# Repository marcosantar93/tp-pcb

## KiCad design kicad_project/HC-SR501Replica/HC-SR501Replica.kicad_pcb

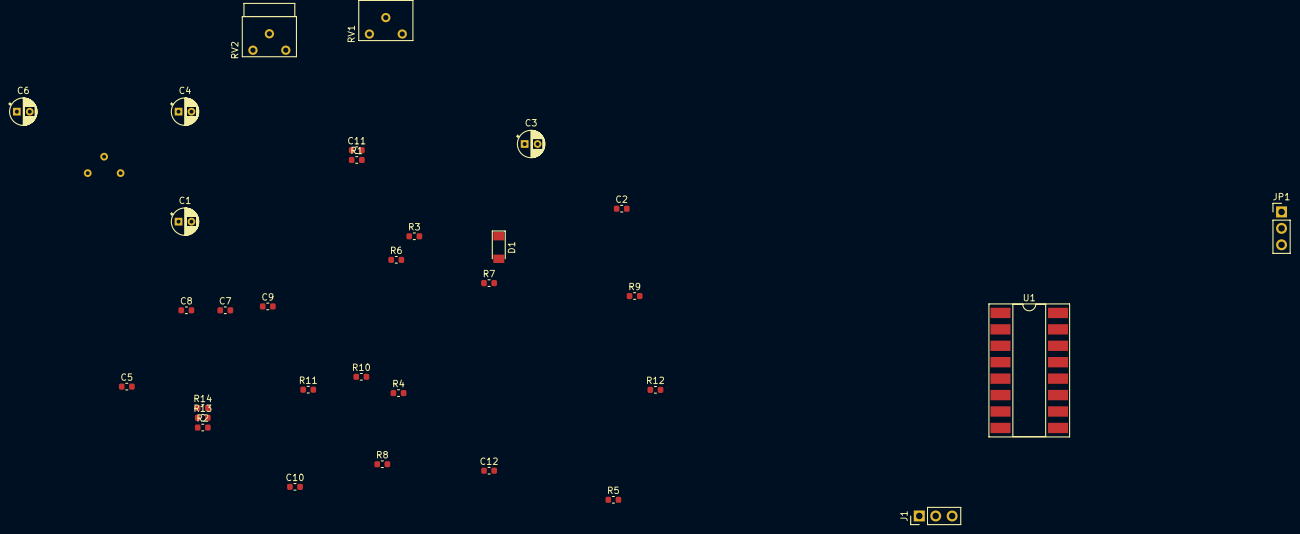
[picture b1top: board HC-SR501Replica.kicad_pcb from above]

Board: 2 copper layers, 33 parts (1 on the bottom side), 26 nets, no tracks yet.

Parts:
C1: 22μ; CP_Radial_D4.0mm_P2.00mm
C2, C5, C8, C10, C11: 103p; C_0603_1608Metric
C3, C4, C6: 47μ; CP_Radial_D4.0mm_P2.00mm
C7, C12: 104p; C_0603_1608Metric
C9: 502p; C_0603_1608Metric
D1: D; D_MiniMELF
J1: Conn_01x03; PinHeader_1x03_P2.54mm_Vertical
JP1: Jumper_3_Bridged12; PinHeader_1x03_P2.54mm_Vertical
PIR1: ZSBG446671; PIR
R1, R13: 10K; R_0603_1608Metric
R2, R4, R6: 18K; R_0603_1608Metric
R3: 47K; R_0603_1608Metric
R5, R10, R12, R14: 1M; R_0603_1608Metric
R7: 12K; R_0603_1608Metric
R8: 470K; R_0603_1608Metric
R9: 6.8K; R_0603_1608Metric
R11: R_PHOTO; R_0603_1608Metric
RV1, RV2: 1M; Potentiometer_Bourns_3339W_Horizontal
U1: BISS0001; DIP-16_W8.89mm_SMDSocket_LongPads

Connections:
+3V3: C1.1, JP1.3, R1.2, U1.8, U1.11
/1IN+: R4.1, U1.14
/1IN-: C5.1, C9.1, R5.1, R6.1, U1.15
/1OUT: C4.2, C5.2, R5.2, U1.16
/2IN-: C8.2, R8.2, R9.1, U1.13
/2OUT: C8.1, RV1.1, RV1.2, U1.12
/OUT: J1.2, U1.2
/ROS: JP1.2, U1.1
GND: C1.2, C2.2, C3.2, C6.2, C10.2, C11.2, C12.2, J1.1, JP1.1, PIR1.1, R3.2, R11.2, R12.2, U1.7
unnamed: C2.1, PIR1.2, R3.1, R4.2
unnamed: C3.1, R1.1, R2.2
unnamed: C4.1, C7.2, R7.2
unnamed: C6.1, R6.2
unnamed: C7.1, R7.1, R9.2
unnamed: C9.2, C10.1
unnamed: C11.1, RV2.2, RV2.3, U1.4
unnamed: C12.1, R14.2, U1.5
unnamed: PIR1.3, R2.1
unnamed: R8.1, RV1.3
unnamed: R10.1, R11.1
unnamed: R10.2, U1.9
unnamed: R12.1, U1.10
unnamed: R13.1, U1.3
unnamed: R13.2, RV2.1
unnamed: R14.1, U1.6
VCC: D1.2, J1.3

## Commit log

2018-09-14 initial
2018-10-19 esquematico casi completo
